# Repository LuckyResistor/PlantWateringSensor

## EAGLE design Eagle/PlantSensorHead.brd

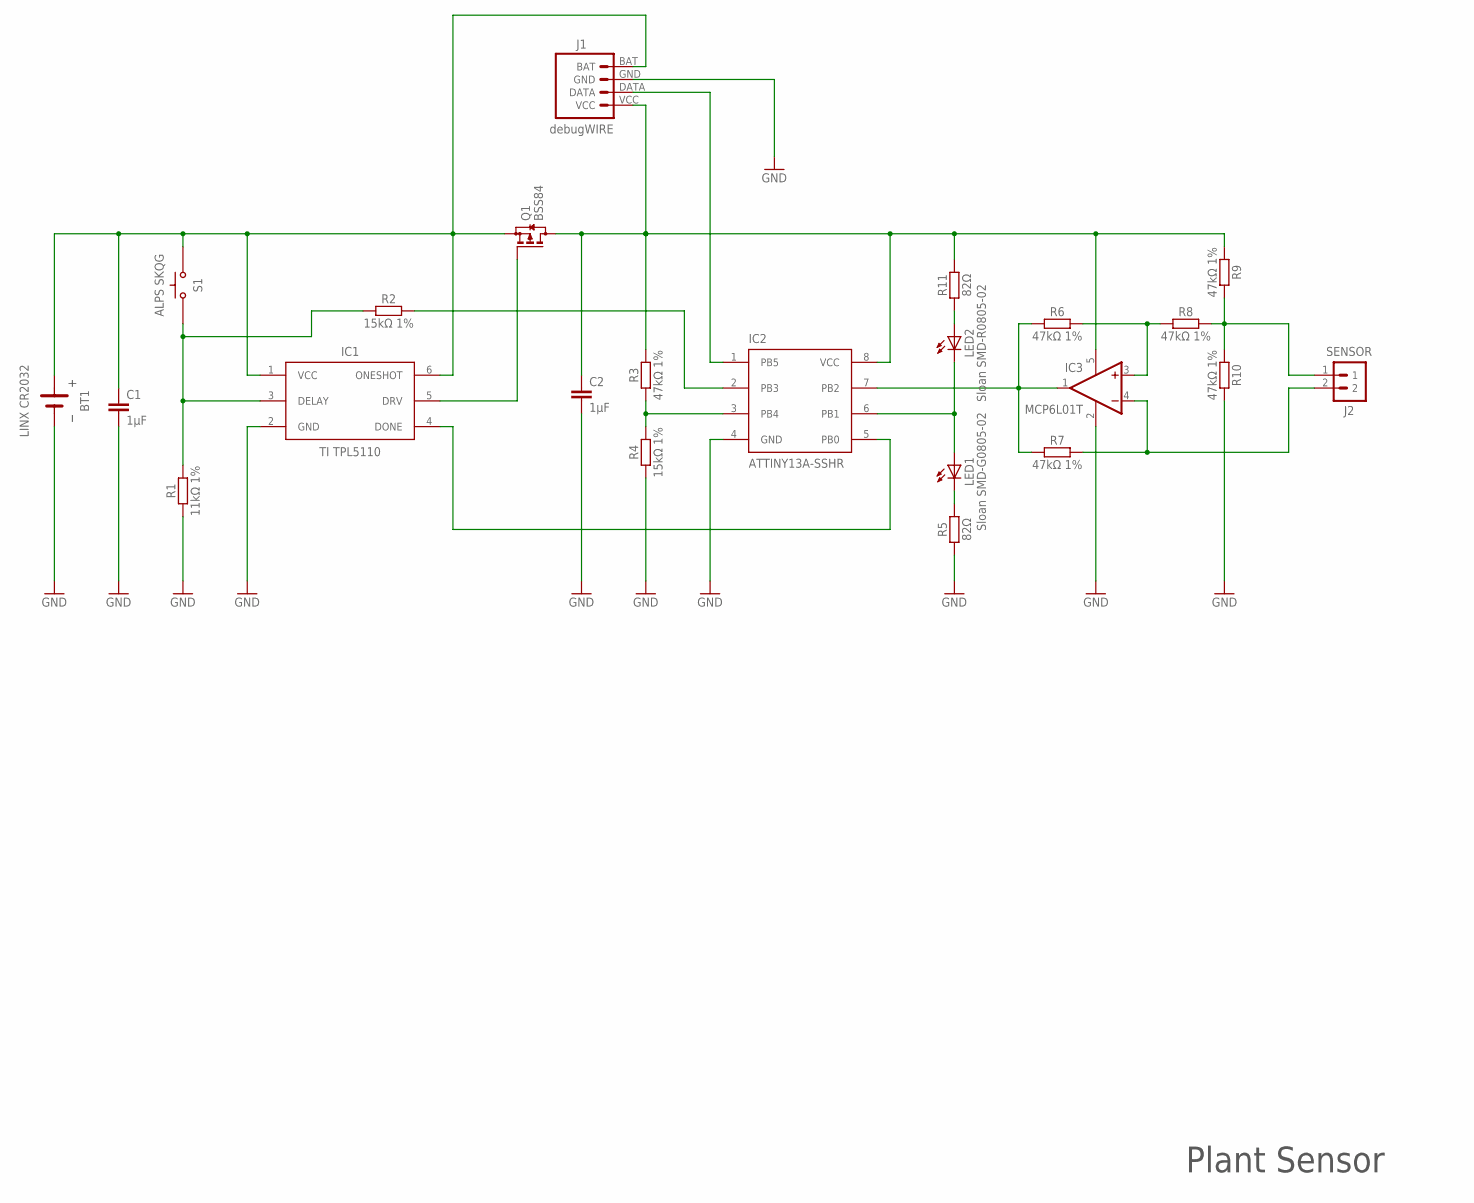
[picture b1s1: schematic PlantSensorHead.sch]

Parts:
BT1: LINX CR2032; LINX-BAT-HLD-001
C1, C2: 1µF; CAPACITOR-0805-MURATA-GRM-21
IC1: TI TPL5110; SOT23-6L
IC2: ATTINY13A-SSHR; SO08_015_JEDEC
IC3: MCP6L01T; SOT23-5
J1: debugWIRE; CON-PADS-DEBUG-WIRE-50
J2: SENSOR; CON_PADS_2XWIRE
LED1: Sloan SMD-G0805-02; LED-0805-SLOAN
LED2: Sloan SMD-R0805-02; LED-0805-SLOAN
Q1: BSS84; SOT23
R1: 11kΩ 1%; RESISTOR-0805-KOA-RK73-2A
R2, R4: 15kΩ 1%; RESISTOR-0805-KOA-RK73-2A
R3, R6, R7, R8, R9, R10: 47kΩ 1%; RESISTOR-0805-KOA-RK73-2A
R5, R11: 82Ω; RESISTOR-0805-KOA-RK73-2A
S1: ALPS SKQG; ALPS_SKQGAKE010

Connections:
BTN: IC1.3 (DELAY), R1.2, R2.1, S1.1, S1.2 (1)
C_FREQ: IC2.7 (PB2), IC3.1 (OUT), R6.2, R7.2
DONE: IC1.4 (DONE), IC2.5 (PB0)
GND: BT1.GND, C1.2, C2.2, IC1.2 (GND), IC2.4 (GND), IC3.2 (V-), J1.GND, R1.1, R4.1, R5.1, R10.1
LED: IC2.6 (PB1), LED1.A, LED2.C
unnamed: LED2.A, R11.1
unnamed: LED1.C, R5.2
unnamed: IC1.5 (DRV), Q1.1 (G)
unnamed: IC2.2 (PB3), R2.2
unnamed: IC3.3 (+IN), R6.1, R8.2
RST: IC2.1 (PB5), J1.DATA
SENS1A: J2.1, R8.1, R9.1, R10.2
SENS2A: IC3.4 (-IN), J2.2, R7.1
VBR: IC2.3 (PB4), R3.1, R4.2
VCCB: BT1.VDD1 (VDD), BT1.VDD2 (VDD), C1.1, IC1.1 (VCC), IC1.6 (ONESHOT), J1.BAT, Q1.2 (S), S1.3 (2), S1.4 (2)
VCCM: C2.1, IC2.8 (VCC), IC3.5 (V+), J1.VCC, Q1.3 (D), R3.2, R9.2, R11.2

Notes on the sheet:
Plant Sensor

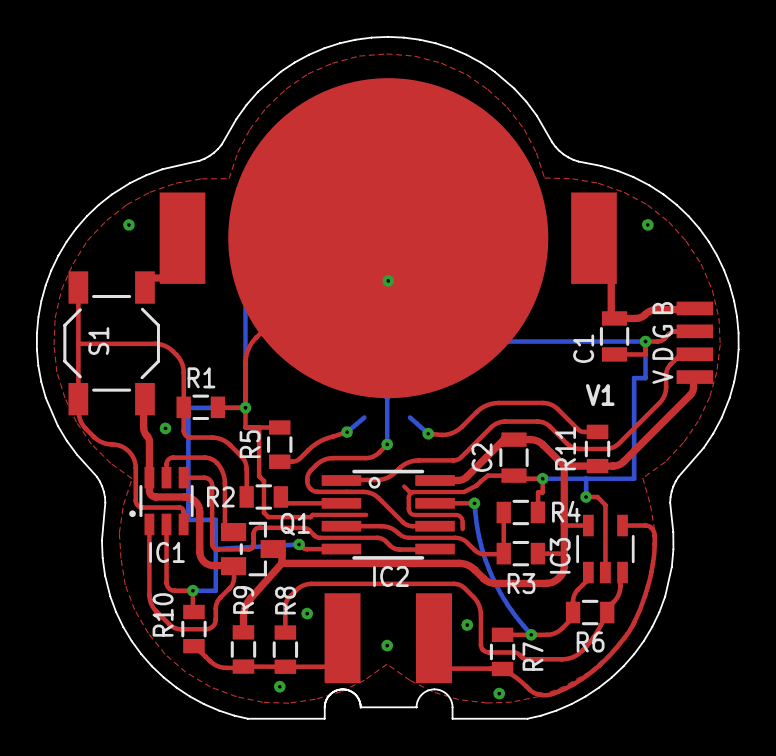
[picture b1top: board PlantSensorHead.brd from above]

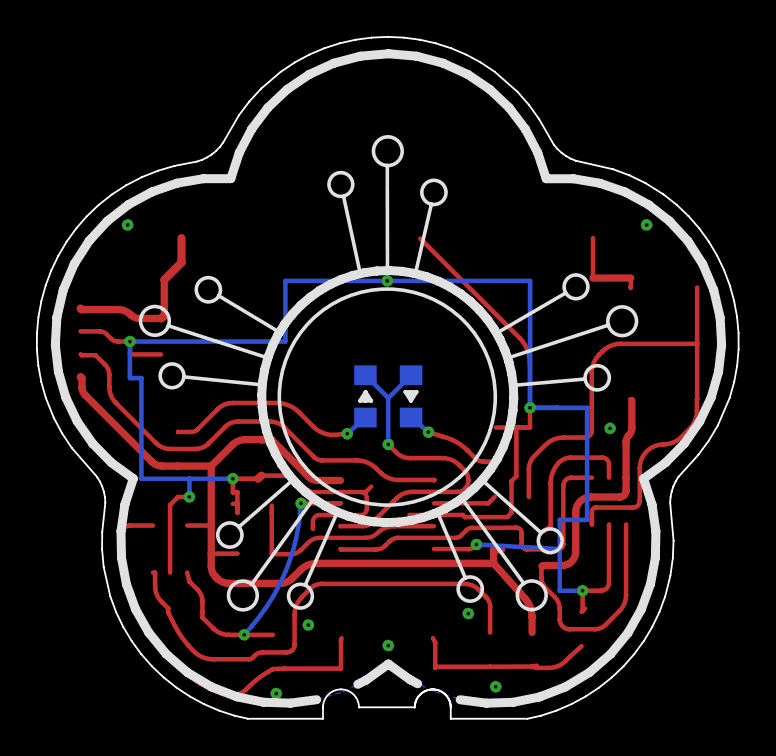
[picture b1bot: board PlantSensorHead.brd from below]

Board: 2 copper layers, 39.0 x 37.9 mm, 23 parts (2 on the bottom side), 16 nets.

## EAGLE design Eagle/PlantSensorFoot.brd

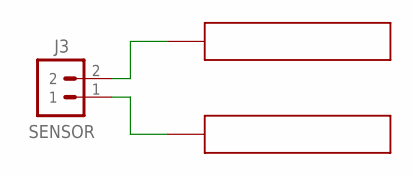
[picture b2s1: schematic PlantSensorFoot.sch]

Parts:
CP1, CP2: CAP_PAD_5X30; CAP_PLATE_5X30
J3: SENSOR; CON_PADS_2XWIRE

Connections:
SENS1B: CP2.1, J3.1
SENS2B: CP1.1, J3.2

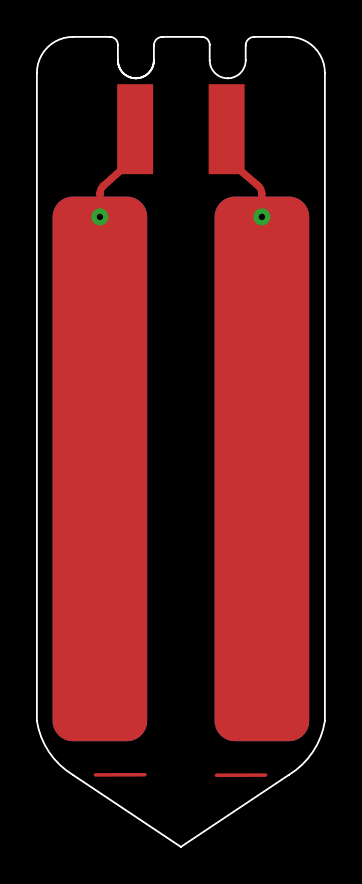
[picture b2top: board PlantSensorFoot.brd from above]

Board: 2 copper layers, 16.0 x 45.0 mm, 3 parts (0 on the bottom side), 2 nets.

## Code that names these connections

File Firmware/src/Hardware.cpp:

//
// Plant Watering Sensor Project
// ---------------------------------------------------------------------------
// (c)2017 by Lucky Resistor. See LICENSE for details.
// https://luckyresistor.me
//
// This documentation describes Open Hardware and is licensed
// under the CERN OHL v. 1.2.
//
// You may redistribute and modify this documentation under the terms of
// the CERN OHL v.1.2. (http://ohwr.org/cernohl). This documentation is
// distributed WITHOUT ANY EXPRESS OR IMPLIED WARRANTY, INCLUDING OF
// MERCHANTABILITY, SATISFACTORY QUALITY AND FITNESS FOR A PARTICULAR
// PURPOSE. Please see the CERN OHL v.1.2 for applicable conditions
//
#include "Hardware.h"


#include "Configuration.h"
#include "Tool.h"

#include <avr/io.h>
#include <avr/common.h>
#include <avr/cpufunc.h>


namespace Hardware {
	

void setup()
{
	// Set the pre-scaler frequency to 2.4MHz.
	CLKPR = _BV(CLKPCE); // First set the CE bit.
	CLKPR = _BV(CLKPS1); // ...then set the clock frequency.
	
	// Setup PORTB:
	// - PB0/Pin 5 as output (done signal).
	// - PB1/Pin 6 keep tristate Hi-Z for the display (LED).
	// - PB2/Pin 7 as input (oscillator) used for counter.
	// - PB3/Pin 2 as input (button).
	DDRB = _BV(DDB0);
	// Make sure all outputs are low.
	PORTB = 0;
	
	// Setup the ADC for PB4/Pin 3
	// - Use the internal 1.1V source.
	// - Left align the result.
	// - Use PB4/Pin 3 as input.
	ADMUX = (_BV(REFS0)|_BV(MUX1));
	// - Enable the ADC (to allow enough time to stabilize)
	// - Prescaler to 128, to get 75kHz which should be get an accurate result.
	ADCSRA = (_BV(ADEN)|_BV(ADPS2)|_BV(ADPS1)|_BV(ADPS0));
	// - Disable the digital in on for PB0, PB1, PB4 to reduce power usage.
	DIDR0 = (_BV(AIN0D)|_BV(AIN1D)|_BV(ADC2D));
	
	// Setup the counter.
	// - no compare match, no PWM, no compare output.
	TCCR0A = 0;
	// - No Interrupt
	TIMSK0 = 0;
}


void setLedState(LedState ledState)
{
	switch (ledState) {
	case LedState::Off:
	default: // Set PB0 to Hi-Z;
		DDRB &= (~_BV(DDB1));
		PORTB &= (~_BV(PORTB1));
		break;
	case LedState::Green: // Set PB0 to HIGH.
		DDRB |= _BV(DDB1);
		PORTB |= _BV(PORTB1);
		break;
	case LedState::Red: // Set PB0 to LOW.
		DDRB |= _BV(DDB1);
		PORTB &= (~_BV(PORTB1));
		break;
	}
}


void sendDoneSignal()
{
	// Just set the done line to high for 10ms.
	PORTB |= _BV(DDB0);
	Tool::delayMs(10);
	PORTB &= ~_BV(DDB0);
	Tool::delayMs(100);
}


bool isButtonPressed()
{
	return ((PINB & _BV(PINB3)) != 0);
}


VoltageValue getVoltageValue()
{
	// Collect a number of samples and get the average out of them.
	uint16_t values = 0u;
	const uint8_t sampleCount = 32u;
	for (uint8_t i = 0; i < sampleCount; ++i) {
		// Start the conversion.
		ADCSRA |= _BV(ADSC);
		// Wait for the conversion to finish.
		while ((ADCSRA & _BV(ADSC)) != 0) {}
		// Read the value.
		uint16_t value = ADCL;
		value |= ((uint16_t)(ADCH) << 8);
		// Add it up to get the average.
		values += value;
	}
	// Return the average of all samples.
	return (values / sampleCount);
}


void shutdownVoltageMeasurement()
{
	// Disable the ADC to save power.
	ADCSRA &= ~_BV(ADEN); // Disable the ADC
	PRR |= _BV(PRADC); // Shutdown the ADC to save power.
}


OscillatorFrequency getOscillatorFrequency()
{
	// Select external clock source, T0/Pin 7 to enable the counter.
	TCCR0B = (_BV(CS00)|_BV(CS01)|_BV(CS02));
	// Calculate the average over 10 measurements.
	uint16_t values = 0;
	const uint8_t sampleCount = 5u;
	for (uint8_t i = 0; i < sampleCount; ++i) {
		// Wait for the first count to synchronize counting.
		TCNT0 = 0;
		for (uint8_t j = 0; j != 0xffu && TCNT0 == 0; ++j) {} // this loop prevent hangs if the oscillator isn't running.
		// Reset the counter.
		TCNT0 = 0;
		// Clear the overflow flag.
		TIFR0 = _BV(TOV0);
		// Wait ~1ms for the result.
		Tool::delayMs(1);
		// Read the result.
		uint8_t value = TCNT0;
		// Check the overflow flag.
		if ((TIFR0 & _BV(TOV0)) != 0) {
			value = 0xff;
		}
		values += value;
	}
	return (values / sampleCount);
}


void shutdownOscillatorCounter()
{
	// Stop the counter and shutdown the module to save power.
	TCCR0B = 0;
	PRR |= _BV(PRTIM0);
}


}

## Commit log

2017-08-23 The initial version of the documentation.

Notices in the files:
Eagle/PlantSensorFoot.brd:
(c)2017 by Lucky Resistor. https://luckyresistor.me
Licensed under CERN OHL v.1.2 or later
